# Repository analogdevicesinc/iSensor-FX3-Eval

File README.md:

# EVAL-ADIS-FX3 Evaluation Software

This repository contains all evaluation software for the EVAL-ADIS-FX3 iSensor evaluation board. The EVAL-ADIS-FX3 is the latest addition to the iSensor evaluation portfolio and was designed from the ground up to provide users with an easy-to-use solution for capturing reliable inertial data in lab and characterization environments. The EVAL-ADIS-FX3 incorporates the ability to capture inertial sensor data at maximum throughput while interfacing with external test equipment and reacting to external triggers.

See the [Quick Start Guide](/src/guide/guide.md) for an overview of eval software functionality, or download the latest [Release](https://github.com/analogdevicesinc/iSensor-FX3-Eval/releases/) installer.

In addition to the dedicated hardware platform, a .NET API and interop wrapper are provided which allow for simple development of custom applications. We’ve included many useful features into the API that enable designers to characterize sensor performance in any .NET compatible environment.

The API documentation for the iSensor FX3Api can be accessed here:

https://analogdevicesinc.github.io/iSensor-FX3-Eval/

The iSensor FX3 Evaluation GUI documentation and user guide has been moved to the official Analog Devices Wiki: 

https://wiki.analog.com/resources/eval/user-guides/inertial-mems/evaluation-systems/eval-adis-fx3

Analog Devices product page:

https://www.analog.com/en/resources/evaluation-hardware-and-software/evaluation-boards-kits/eval-adis-fx3.html

## Supporting Documentation

Hardware design files for the evaluation board are provided in the /hardware directory.

The custom windows driver installer is provided in the /drivers directory

Register map definition files for all supported iSensor products are provided in the /RegMaps directory

# iSensor FX3Api Wrapper [src_wrapper](/src_wrapper)

The wrapper library provides a simplified interface to configure and capture data from an ADI IMU. This interface can be used in the .NET ecosystem, or with languages which support .NET interop, such as Python, Matlab, and Labview.

# iSensor FX3 Evaluation GUI [src](/src)

Source code for the iSensor-FX3-Eval IMU evaluation GUI. This is a Winforms application, built on the iSensor-FX3-API. Developed for minumum .NET framework 4.5

## iSensor FX3 Eval GUI - Developer Setup Guide

The iSensor FX3 Eval GUI can be easily compiled and modified without purchasing any software or IDE.

### Prerequisites

Before attempting to compile the iSensor FX3 Eval GUI, ensure that the FX3 Driver is installed. This can be downloaded from the wiki (linked above)

The iSensor FX3 Eval GUI is currently Windows only. It requires Microsoft .NET framework 4.5 or newer to be installed.

### Development Environment

The iSensor FX3 Eval GUI can be compiled and modified using the Visual Studio IDE. Visual studio community is fully featured and available for free use on open source projects

https://visualstudio.microsoft.com/vs/community/

License: https://visualstudio.microsoft.com/license-terms/mlt031819/

### Building

1. Clone the iSensor FX3 Eval repository using the git client of your choice. Note, this repo has the iSensor FX3 API as a submodule dependency, which must be initialized as well. This can be done from Git bash using the following single command:
   - git clone --recurse-submodules https://github.com/analogdevicesinc/iSensor-FX3-Eval.git
2. Open the project file within Visual Studio. File -> Open -> Project/Solution -> Browse for iSensorFX3Eval.vbproj within the src/ folder of the repository
3. Build the project by right clicking on the iSensorFX3Eval project within the visual studio solution explorer and clicking "Build"

That's it! Now you can run and debug within the iSensor FX3 GUI. To make modifications to any forms included within the GUI, simply right click on the form in the solution explorer, and select "View Designer". This will open the GUI designer tool for that form. The startup form is set to "TopGUI.vb"

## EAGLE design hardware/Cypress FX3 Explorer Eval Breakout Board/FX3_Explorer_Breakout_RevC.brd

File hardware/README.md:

# iSensor FX3 Evaluation Hardware

## Overview

The FX3 firmware was initially developed using a Cypress EZ-USB FX3 SuperSpeed Explorer Development Kit and targeted the CYUSB3014/CYUSB2014 family of USB interface ICs offered by Cypress Semiconductor.

## SuperSpeed Explorer Development Kit Breakout Board

A breakout board designed for interfacing iSensor devices with the Cypress SuperSpeed Explorer Kit ([CYUSB3KIT-003](https://www.cypress.com/documentation/development-kitsboards/cyusb3kit-003-ez-usb-fx3-superspeed-explorer-kit)) was introduced as a temporary solution to aid software development. The breakout board design was very simple and only included a 16-pin,2mm connector and a header for probing the digital communication signals. 

The breakout board design files can be found in the hardware folder of this repository ([link](Cypress FX3 Explorer Eval Breakout Board)).

## SuperSpeed Explorer Kit Jumper Configuration

**Three** jumpers **must** be installed on the SuperSpeed Explorer Kit as shown below to operate correctly. **Jumpers J2, J3, and J5 must be installed** when using the SuperSpeed Explorer Kit. **Jumper J4 must be open** to allow booting from the onboard EEPROM. 

## EVAL-ADIS-FX3

Once the project's hardware requirements matured, the [EVAL-ADIS-FX3](https://www.analog.com/en/design-center/evaluation-hardware-and-software/evaluation-boards-kits/eval-adis-fx3.html) was developed. This design reduced the size and cost of the original development platform while adding additional features tailored for IMU applications. 

The EVAL-ADIS-FX3 features include:

- A dedicated, onboard 3.3V, 2A linear regulator designed for high-transient applications
- A USB-C connector (USB 2.0 compatible only)
- An onboard, field-upgradable EEPROM with USB bootloader fallback
- A software-selectable OFF / 3.3V / 5V IMU supply output with overcurrent and short protection
- A JST-XH-2 external supply connector
- Selectable USB and external supply selection
- Onboard status LEDs for each IMU GPIO pin
- An iSensor standard, 16-pin, 2mm connector for compatibility with existing iSensor breakout boards and adapters
- An additional 10-pin, 2mm connector for feature expansion. As of writing, the firmware and API include support for:
- FX3 UART debugging
- Four additional GPIO pins for external test equipment triggering and sensing (separate from the IMU GPIOs)
- Separate 3.3V and 5V supplies from the DUT supply meant to power external level shifters, drivers, interface ICs, etc.
- An extra, “bit-banged” SPI port to allow for “non-standard” SPI configurations and communication with external hardware (ADCs, DACs, protocol interface ICs, etc.)
- An I2C port meant for interfacing with I2C-compatible inertial sensors
- Concurrent, multi-board data capture capability. Multiple EVAL-ADIS-FX3 boards can be connected to the same PC and can concurrently capture data independently of each other
- Very low CPU usage while capturing data, even on older Windows machines
- Windows 7, 8, and 10 compatibility
- 1.5“ x 1.75” PCB footprint

The EVAL-ADIS-FX3 design files can be found in the hardware folder of this repository ([link](EVAL-ADIS-FX3_RevC)).

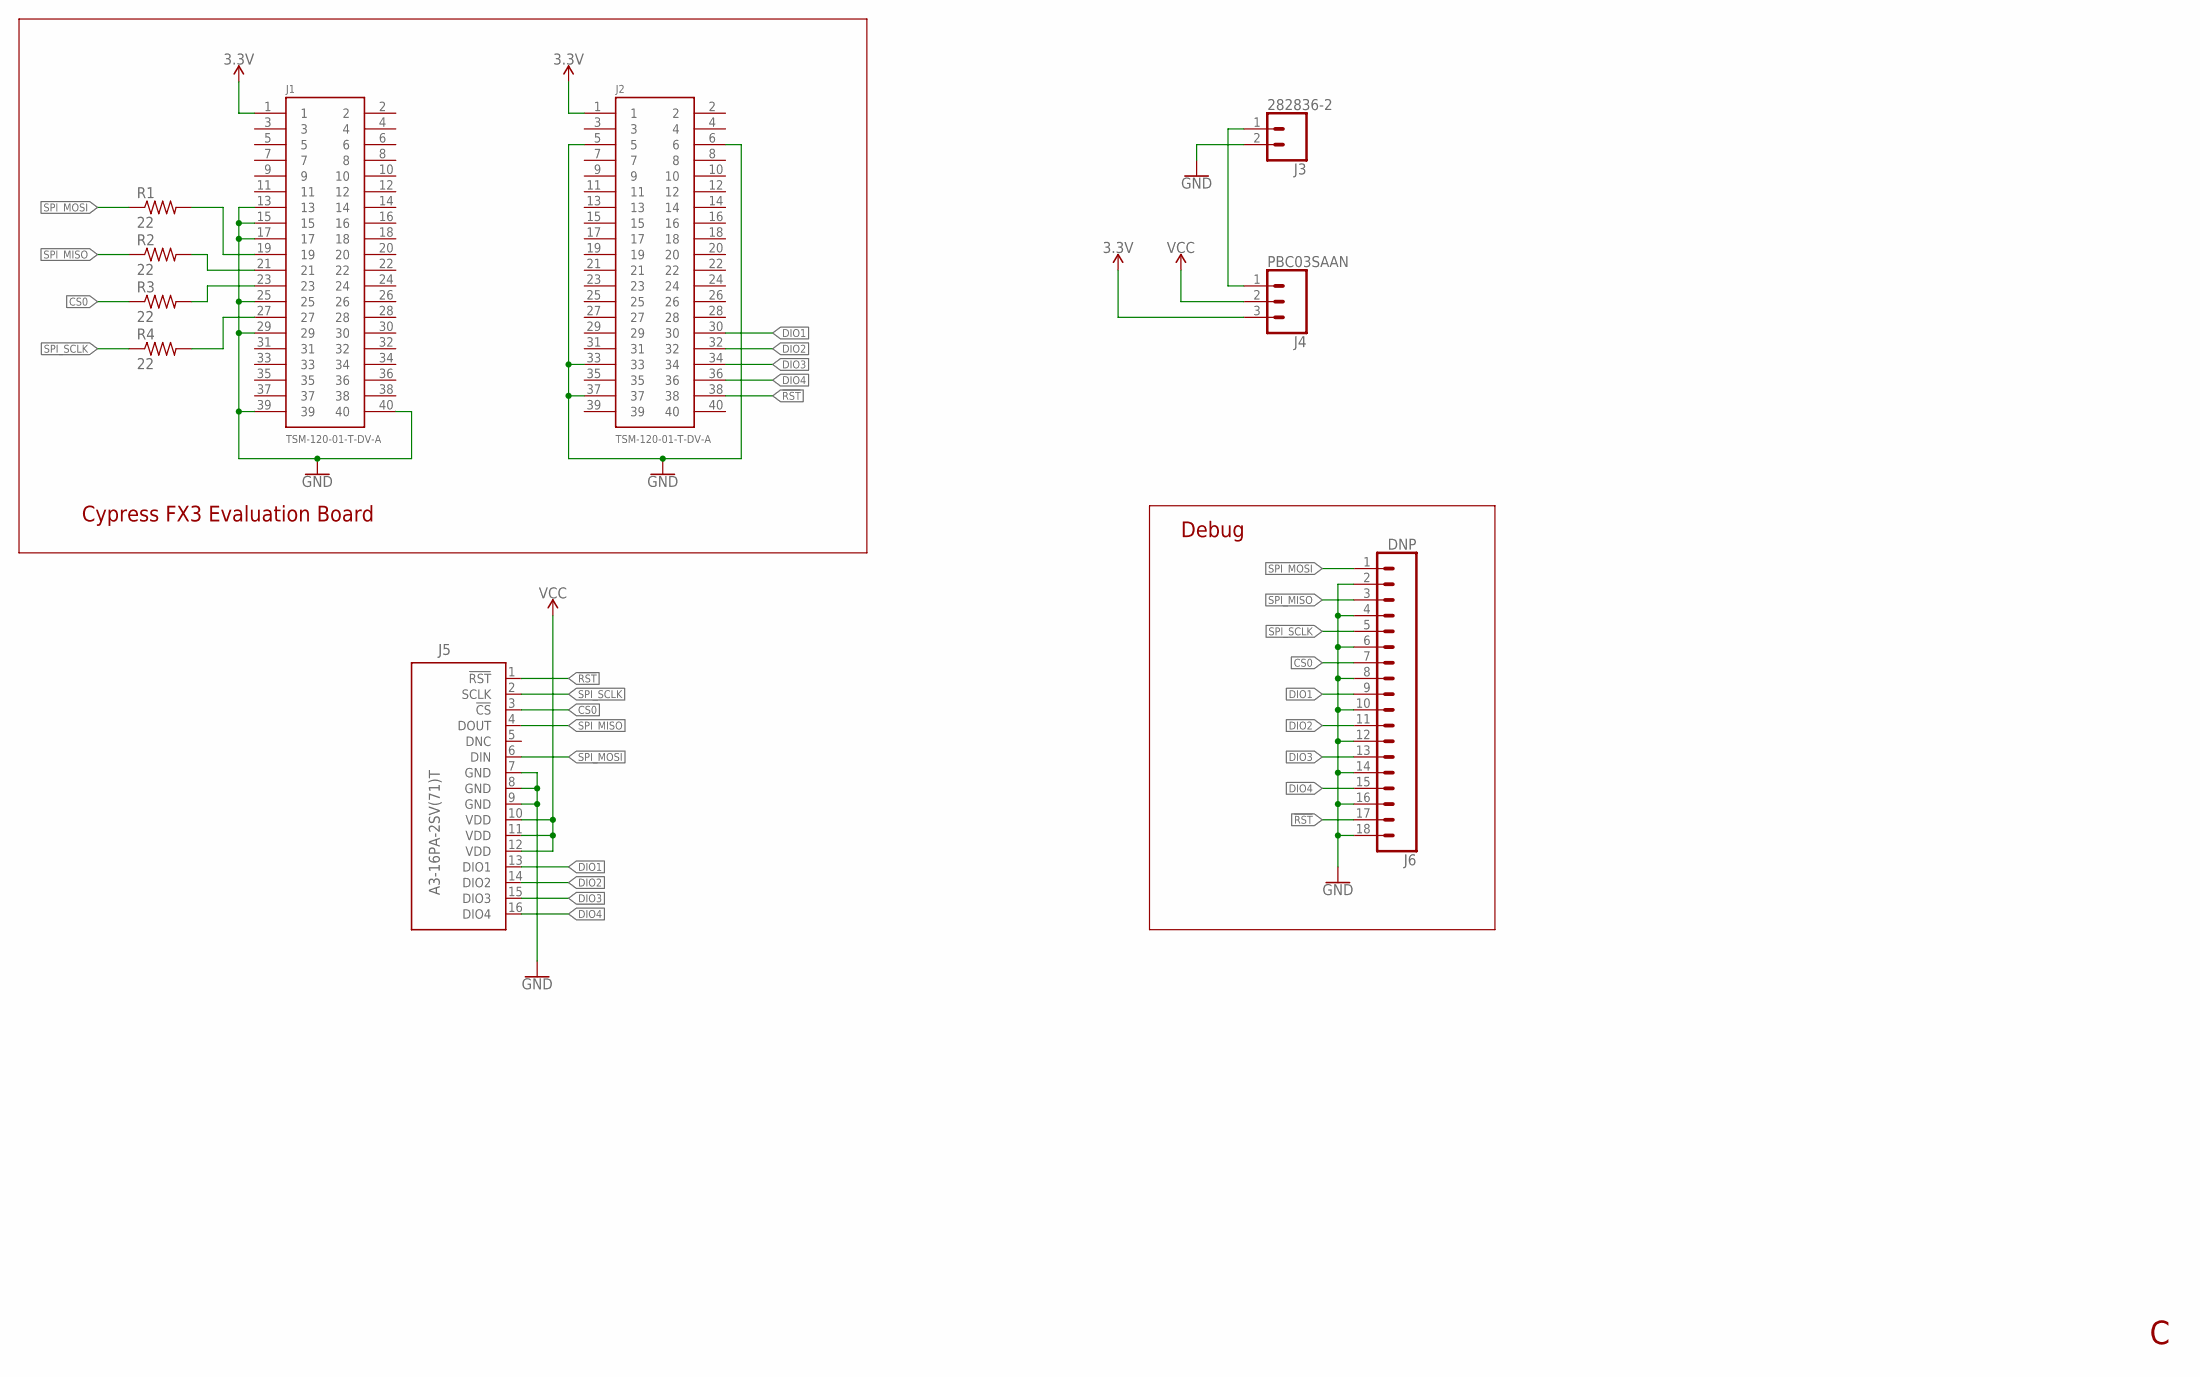
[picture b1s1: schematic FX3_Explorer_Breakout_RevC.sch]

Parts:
J1, J2: TSM-120-01-T-DV-A; TSM-120-XX-XXX-D; PARTNO TSM-120-01-T-DV-A
J3: 282836-2; SCREWTERMINAL-5MM-2; PARTNO 282836-2
J4: PBC03SAAN; 1X03; PARTNO PBC03SAAN
J5: A3-16PA-2SV(71)T; A3-16PA-2SV(71)-TOP; PARTNO A3-16PA-2SV(71)
J6: DNP; 1X18
R1, R2, R3, R4: 22; R0603; PARTNO RC0603FR-0722RL

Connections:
3.3V: J1.1, J2.1, J4.3
!RST: J2.38, J5.1 (!RST), J6.17
CS0: J5.3 (!CS), J6.7, R3.1
DIO1: J2.30, J5.13 (DIO1), J6.9
DIO2: J2.32, J5.14 (DIO2), J6.11
DIO3: J2.34, J5.15 (DIO3), J6.13
DIO4: J2.36, J5.16 (DIO4), J6.15
GND: J1.13, J1.15, J1.17, J1.25, J1.29, J1.39, J1.40, J2.5, J2.6, J2.33, J2.37, J3.2, J5.7 (GND), J5.8 (GND), J5.9 (GND), J6.2, J6.4, J6.6, J6.8, J6.10, J6.12, J6.14, J6.16, J6.18
unnamed: J1.19, R1.2
unnamed: J1.21, R2.2
unnamed: J1.23, R3.2
unnamed: J1.27, R4.2
unnamed: J3.1, J4.1
SPI_MISO: J5.4 (DOUT), J6.3, R2.1
SPI_MOSI: J5.6 (DIN), J6.1, R1.1
SPI_SCLK: J5.2 (SCLK), J6.5, R4.1
VCC: J4.2, J5.10 (VDD), J5.11 (VDD), J5.12 (VDD)

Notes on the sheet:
Cypress FX3 Evaluation Board
Debug

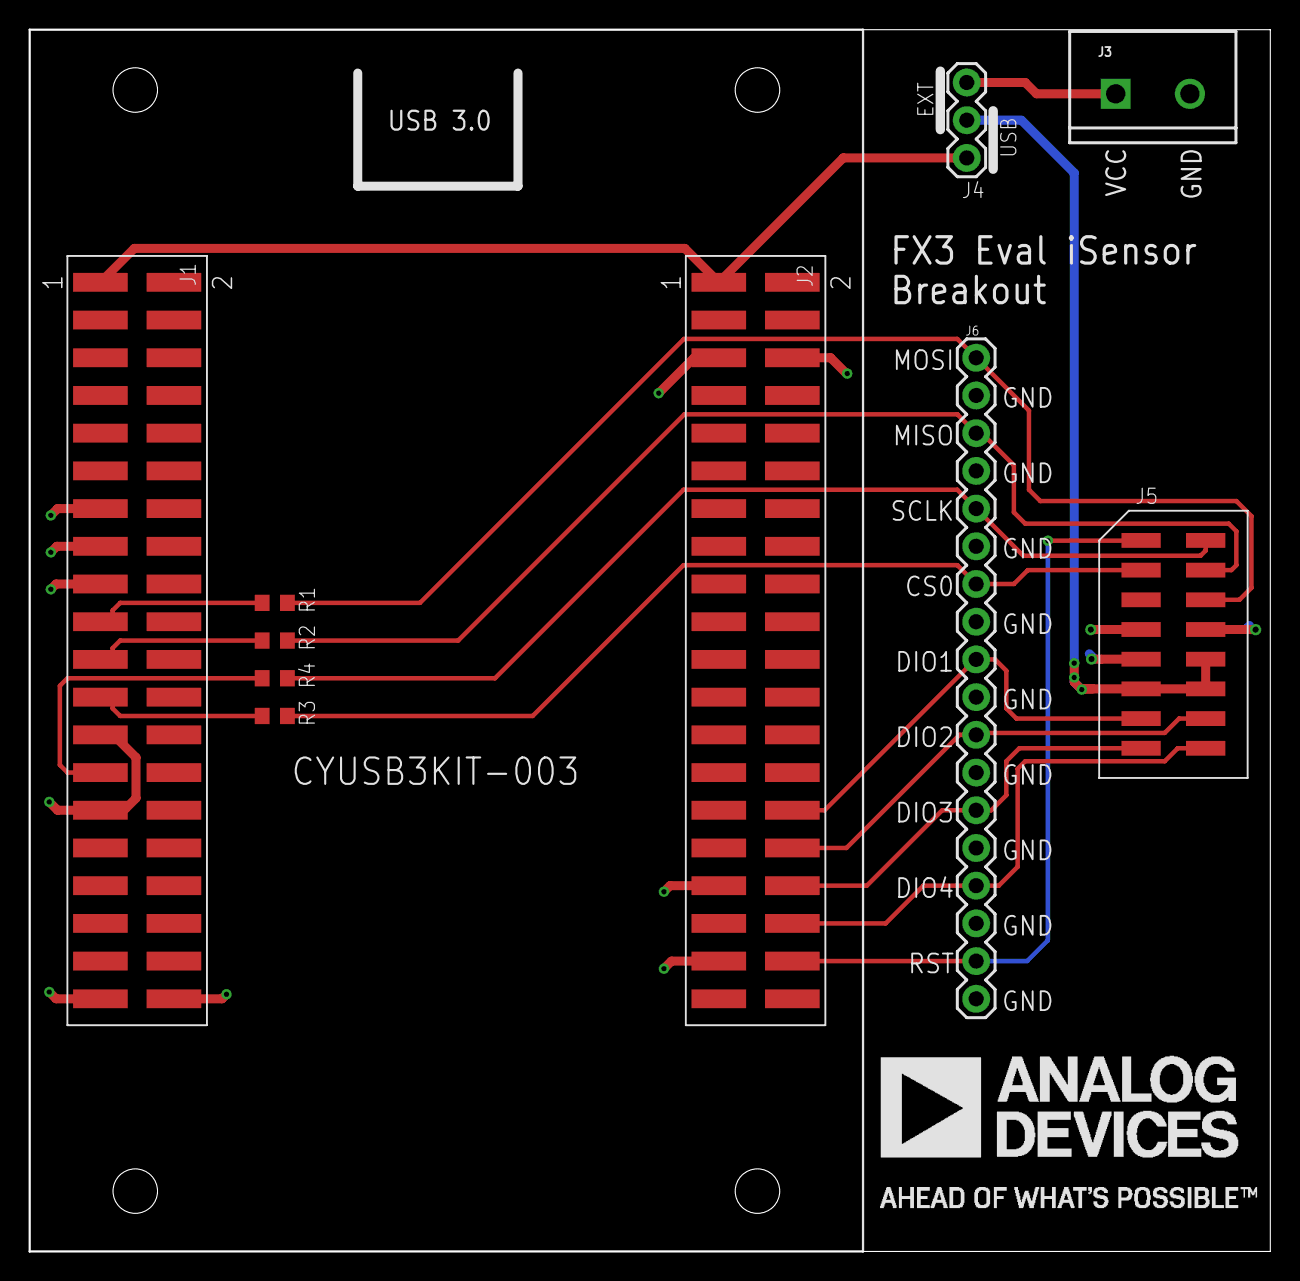
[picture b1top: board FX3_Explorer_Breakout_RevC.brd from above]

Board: 2 copper layers, 83.6 x 82.3 mm, 11 parts (0 on the bottom side), 17 nets.

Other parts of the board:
DRILEGEND: DRILEGEND

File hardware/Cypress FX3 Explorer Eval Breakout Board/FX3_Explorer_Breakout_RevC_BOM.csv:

Qty-1,Part References,Mfg Part Num,Mfg Name,VID,Vendor Part Num,Description,,,,
4,"R1, R2, R3, R4",RC0603FR-0722RL,Yaego,DK,311-22.0HRCT-ND,RES SMD 22 OHM 1% 1/10W 0603,,,,
1,J3,282836-2,TE Connectivity,DK,A98076-ND,TERM BLOCK 2POS SIDE ENTRY 5MM,,,,
1,J5,A3-16PA-2SV(71),Hirose Electric Co Ltd,DK,H10940-ND,CONN HEADER 16POS 2MM GOLD SMD,,,,
1,J6,*,*,*,*,*,,,,
1,J4,PBC03SAAN,Sullins Connector Solutions,DK,S1011E-03-ND,"Connector Header Through Hole 3 position 0.100"""" (2.54mm)",,,,
2,"J1, J2",TSM-120-01-L-DV,Samtec Inc,DK,SAM10308-ND,.025 SQ. TERMINAL STRIPS,,,,
1,,SPC02SYAN,Sullins Connector Solutions,DK,S9001-ND,CONN JUMPER SHORTING GOLD FLASH,,,,

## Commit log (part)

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2020-07-31 Made it so when multiple FX3s are available, form remembers the last FX3 connected and selects that board by default from the drop down menu
2020-07-31 Updated version
2020-08-22 Updated bit bang SPI to allow user to select secondary GPIO for bit bang SPI port'
2020-08-25 Changed charts to init with no series. Fixed exception when you click apply -3db lines with no data
2020-08-27 Updated FX3 resource versions, updated version number to 2.9.0.0
2020-09-03 Fixed registers in the 50x register map
2020-09-10 Removed check that DR pin is high in check DUT connection. Explicitly disable DRActive property on FX3 prior to check, and re-enable after
2020-09-10 Added confirmation message for enabling 5V DUT supply when DUT type is not automotive SPI
2020-09-10 Updated Readme to point to the ADI Wiki
2020-09-15 Fixed it so series count is actually incremented
2020-09-15 Adjusted shutdown procedure for frequency plot GUI
2020-09-15 Changed fixed time to fixed duration to make more clear
2020-09-15 Moved all init code from constructor to load event handler
2020-09-16 Added logic to allow dut selection from a user supplied personality file. This simplifies setting up the GUI significantly (just a single drop down selects reg map, IDUTInterface, SPI parameters)
2020-09-16 Fixed having wrong regmap linked for 49x
2020-09-17 Added supply mode and VDDIO to DUT personality
2020-09-18 Added column to allow manual setting of register scale factor for data plotting form
2020-09-18 Added ability to set custom y-axis labels
2020-09-18 Set minimum app size for data plotter
2020-09-22 Updated dut_personalities.txt
2020-09-22 Re-organized non-code resource files into folders within source
2020-09-22 Deleted unused source file
2020-09-22 Added more sensor register maps
2020-09-22 Changed default regmap directory to regmap folder
2020-09-23 Added 48x regmaps to project
2020-09-23 Update DUT personality with new regmap path when manually selected
2020-09-25 Implemented optional data scroll bar and upreved
2020-09-25 Added title with NFFT, averages, and Fs to frequency plotting utility
2020-09-26 Major GUI front end overhaul. Register access moved to top form. Content is now split into tabs based on functionality
2020-09-26 Upreved, fixed issue where rebooting fx3 with cont read would cause crash
2020-09-27 Pulled all GPIO interfacing forms into a single form, within the tab. Deleted three previous forms
2020-09-27 Fixed issue where app would crash when FX3 disconnected during read
2020-09-28 Moved manual GPIO access to advanced tab. Fixed issue where starting a PWM signal on the data ready pin would cause an exception during check DUT connection
2020-09-28 Added register list to data plot tab
2020-09-30 Fixed implicit coversion issue causing data plot to close slowly. Should probably compile this project under option strict at some point
2020-10-05 Decreased min size to minimum which avoids button clipping. Want to avoid issues when people use a potato computer with 768 vertical pixels (like my personal laptop)
2020-10-06 Fixed issue where changing the Dr pin didnt actually change the selected DR pin in the FX3 object
2020-10-09 Resolved issue where playback would take a long time to start
2020-10-13 Changed to FX3 API 2.9.2
2020-10-28 Changed default stall time for adcmxl products to 18us
2020-11-05 Fixed issue where personality would be applied prior to fx3 connecting
2020-11-09 Uprev'd GUI
2020-11-09 Added support for component SPI interface in GUI (via personality files)
2020-11-10 Excluded component sensor from page reg check
2020-11-17 Added logic to ensure the dr active setting within the logging forms matches the fx3 setting
2020-11-24 Added helper utility to generate CRC4 used by ADXC1500
2020-11-30 Added cypress software license file for CyUSB.dll
2020-12-01 Made it so validate dr check box follows dr active by default
2020-12-01 Updated remote url for release update check, update crc4 builder to allow copying to clipboard
2020-12-02 Added more tool tips for top level GUI
2020-12-02 Made it so navigating to a slide without an image clears the loaded image. Updated guide text with some placeholders
2020-12-09 Upreved GUI to 2.9.3.1
2020-12-21 Set FX3 to strip MISO response during burst trigger by default
2021-01-18 Added application space 0 to scratch reg list
2021-02-04 Moved welcome guide to bottom of form
2021-02-04 Added support for nulling the DC component of an FFT plot
2021-02-09 Adjusted form load to show welcome form as a blocking dialog
2021-03-10 Changed the data streaming GUIs to apply their data ready active setting to the FX3 on activation (rather than the other way around)
2021-04-12 Updated to FX3 API v2.9.4
2021-04-22 Deleted documentation folder. All images are hosted on the ADI wiki now
2021-05-12 Corrected default values listed in the regmap for the 44x, 46x, 50x family of parts to include zero of the bias regs
2021-05-13 Added file copyright header
2021-05-13 Corrected the burst register order for ADIS1650x
2021-05-28 Increased revision
2021-07-19 Moved to using git submodules to maintain dependency on FX3 API, rather than having duplicate copies of the release binaries sorted in the /resources folder. Removed extra DLLs from resources folder
2021-07-19 Updated readme to include build instructions with submodule
2021-07-22 Added parent field to the DUT personality class. This is used to track the generic product line
2021-07-22 Renamed a couple register map files for consistency
2021-07-22 Added gyro, accel, and temperature scale factors to all IMU register maps
2021-07-22 Fixed bug where switching from a multipage regmap to a single page regmap would cause the regview to fail to load properly
2021-07-22 Added default FIR filter values to all 49x/48x register maps. Cleaned up other default values to align with the datasheet
2021-07-22 More general refactoring to improve code readability
2021-08-11 Added DoEvents call to form closing routines
2021-08-11 Fixed issue in the select DUT form where a null reference could potentially occur during first time startup, when no default personality is provided
2021-08-16 Fixed issue where custom personality would be lost if the FX3 board was unexpectedly disconnected
2021-08-16 Made some adjustments to the data ready read timer disable functionality to reduce potential for conflict when operating with a low data ready frequency
2021-09-23 Fixed issue where the read page button would not properly validate SPI data - this is why functions should only have a single exit point. Also made it so state vector exceptions are not printed, they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
2021-10-14 Changed ADIS16210 default SCLK to 830KHz and stall to 40us to match the datasheet. Added X accel null register as a possible scratch register for testing SPI communications
2021-10-18 Corrected the names again. The names in the datasheet are not consistent in their usage of an _ between the axis and the register label
2021-10-25 Updated ADcmXL302x REC_CTRL1 register to REC_CTRL to match datasheet
2021-10-29 Made a slight tweak to how the DutPersonality class parses the personality CSV files to allow for backwards compatibility with personality files that are missing some fields
2021-11-23 Updated tool tips
2021-11-24 Corrected issue where the NFFT would not be properly restored from settings
2021-12-21 When disabling the axis autoscaling the in data plotter, the current min and max are copied to the text boxes. This allows the user to quickly set the scale, then lock the scale in
2022-01-13 Updated colors again to provide greater variety
2022-06-24 Started work on refactoring the time series plotter application to allow for multiple plot views in one chart
2022-06-24 Updated version number to 2.9.5.4
2022-06-24 Added new controls for configuring the burst format
2022-06-26 Added personality and register maps for the ADIS1654x and ADIS1655x product lines
2022-06-26 Added DELTA scale factors. Removed scale factors from the generic x regmap, for consistency with other products
2022-06-26 Implemented data packet parsing. Connected burst manager to the adisInterface and FX3 as appropriate. Implemented functions to configure the FX3 and DUT based on the desired burst settings
2022-06-27 Moved update to burst registers to after applying property
2022-06-27 Excluded registers which are not readable or writeable from being displayed (cant do anything with them)
2022-06-27 Corrected issue with the register list parsing
2022-06-28 Updated welcome guide to reflect the changes to the plotter and burst read forms
2022-06-29 Updated submodule to latest
2022-07-19 Removed lines per write option
2022-08-04 Updated working assembly rev
2022-09-30 Adjusted the write register map function to allow for signed inputs
2022-10-06 Adjusted the IMU burst read form to give a different error message for unknown IMU vs IMU which does not support burst reads
2022-11-22 Error logs are now saved to app current directory. Added exception message to the popup. This addresses issue where application may not have permissions to write to the appdata folder (this can also 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
2023-05-18 Added driver installer
2023-07-26 Moved all regmaps to top level directory
2023-07-26 Updated gitignore to remove files which are no longer used. Allowed adding sln file
2023-07-26 Added wrapper project to SLN
2023-07-26 Fixed naming convention for repo
2023-07-26 Added docs link to readme
2023-08-23 Fixed issue where loading a customer register map from a path which contains a comma would fail to save, due to the use of a CSV file for setting storage. Path commas are now replaced by a token.
2023-09-25 Added const string for the custom personality name to get rid of hard coded strings in application logic
2024-08-07 Added register definitions and personality entries for ADIS16501-2, ADIS1657x family
2024-08-08 Added null check before setting regmap path
2024-08-12 Added ADIS1657x family support to the burst logger app
2024-10-24 Adding more helpful content to the readme
2024-11-26 Updated formatting
2024-11-26 Set data to int instead of double
2025-01-15 Updated ADIS16210 example to enable decimation filter and data ready triggered sampling
2025-01-16 Added default plot regs field to personality
2025-01-16 Added StreamDataLogger project to this repo. Intent is to include reference usage in the wrapper, for streaming to a file. Also added support for scaling data to the logger
2025-01-16 Added scale data and timestamp data selection options to register logging application. Also grouped relevant settings into boxes for readability
2025-01-16 Fixed issue with timeout not being applied
2025-01-17 Updated control spacing to be more even
2025-01-17 Fixed issue with setting the plotindex variable for default plot regs. Updated logic to allow multiple register matches to be assigned to the same plot view
2025-01-17 Added default plot registers for most active devices
2025-01-21 Caps fix
2025-01-21 Corrected function to public
2025-01-21 Consolidated Data Plotting and Data Logging tabs to single Data Capture tab
2025-01-21 Fixed plot labels not loading correctly for multiple default plot windows
2025-01-22 Made a few functional changes to the plotter. Text values only update at 2Hz while plotting now. Changing the text at high rates does not work well and will lag the plot view. Also removed the scale 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
2025-01-22 Adjusted UI element placement. Made regview and settings slightly smaller
2025-01-22 Change csv datalog title to include product name
2025-01-22 Fixed being able to draw plot labels offscreen
2025-01-22 Remove point markers when changing from log scale to non-logscale plotting
2025-01-22 Removed iSensorSPIBuffer and components from personality definition. All worked, but are not well supported via hardware and not recommended. Regmap definition files are remaining in the repo
2025-01-23 Swapped utilities and settings groups. Less mouse movement
2025-01-28 Added bit width display to register logger
2026-05-01 updated ADIS16607 regmaps

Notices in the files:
parts and their libraries:
SparkFun-Connectors: Licensing: Creative Commons ShareAlike 4.0 International - https://creativecommons.org/licenses/by-sa/4.0
